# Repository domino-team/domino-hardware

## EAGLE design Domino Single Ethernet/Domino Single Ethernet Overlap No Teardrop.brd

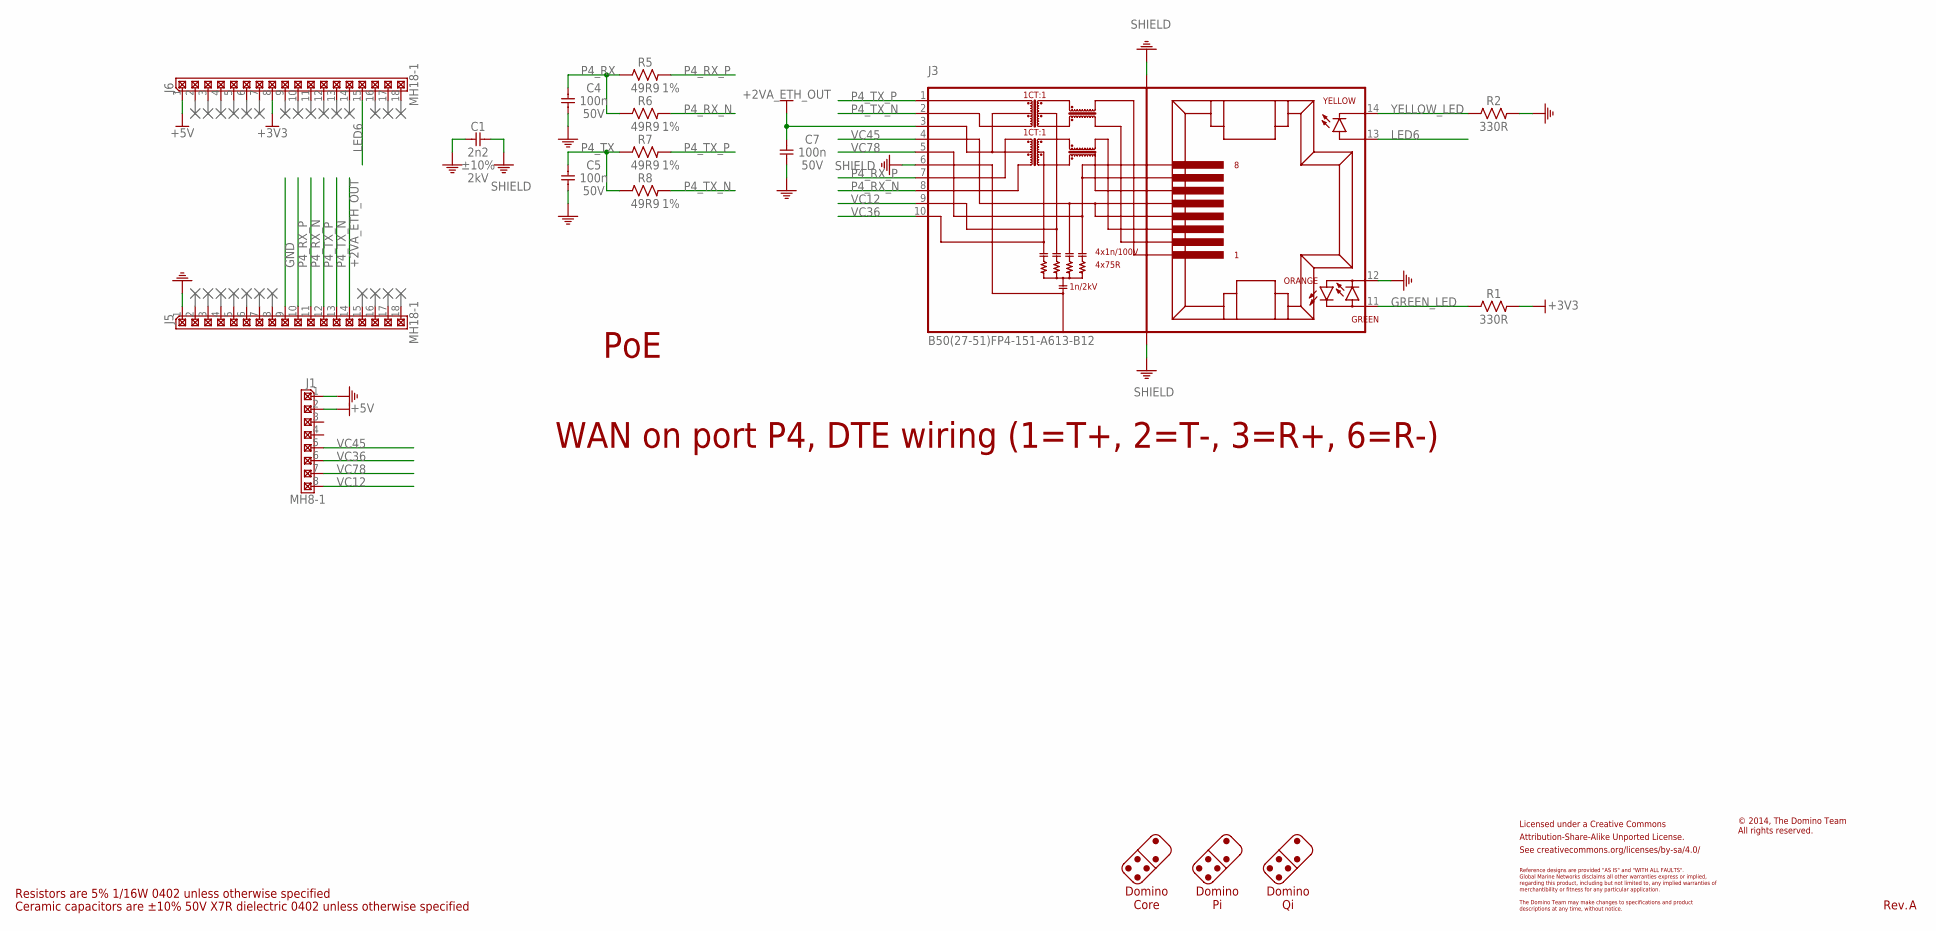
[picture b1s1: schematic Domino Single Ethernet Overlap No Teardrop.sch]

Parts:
C1: 2n2; C1206; PARTNO C1210_2n2_X7R_10%_CER_2kV
C4, C5, C7: 100n; C0402; PARTNO C0402_100n_X7R_10%_CER_50V
CC-BY-SA1: CC-BY-SA_LOGO
J1: MH8-1; MH8-1-0.1
J3: B50(27-51)FP4-151-A613-B12; PARTNO B50(27-51)FP4-151-A613-B12
J5, J6: MH18-1; MH18-1-0.1
R1, R2: 330R; R0402; PARTNO R0402_330R_5%_62.5mW
R5, R6, R7, R8: 49R9; R0402; PARTNO R0402_49R9_1%_62.5mW

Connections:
+2VA_ETH_OUT: C7.2, J3.3, J5.14
+3V3: J6.8, R1.2
+5V: J1.2, J6.1
GND: C1.1, C4.1, C5.1, C7.1, J1.1, J3.12, J5.1, J5.9, R2.2
GREEN_LED: J3.11, R1.1
LED6: J3.13, J6.15
P4_RX: C4.2, R5.1, R6.1
P4_RX_N: J3.8, J5.11, R6.2
P4_RX_P: J3.7, J5.10, R5.2
P4_TX: C5.2, R7.1, R8.1
P4_TX_N: J3.2, J5.13, R8.2
P4_TX_P: J3.1, J5.12, R7.2
SHIELD: C1.2, J3.6, J3.SH$1 (SHIELD), J3.SH$2 (SHIELD)
VC12: J1.8, J3.9
VC36: J1.6, J3.10
VC45: J1.5, J3.4
VC78: J1.7, J3.5
YELLOW_LED: J3.14, R2.1

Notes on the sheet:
Ceramic capacitors are ±10% 50V X7R dielectric 0402 unless otherwise specified
Resistors are 5% 1/16W 0402 unless otherwise specified
Licensed under a Creative Commons
Attribution-Share-Alike Unported License.
See creativecommons.org/licenses/by-sa/4.0/
Reference designs are provided "AS IS" and "WITH ALL FAULTS".
regarding this product, including but not limited to, any implied warranties of
The Domino Team may make changes to specifications and product
Global Marine Networks disclaims all other warranties express or implied,
merchantibility or fitness for any particular application.
descriptions at any time, without notice.
Domino Core
Domino Pi
Domino Qi
© 2014, The Domino Team All rights reserved.
Rev.
WAN on port P4, DTE wiring (1=T+, 2=T-, 3=R+, 6=R-)
PoE

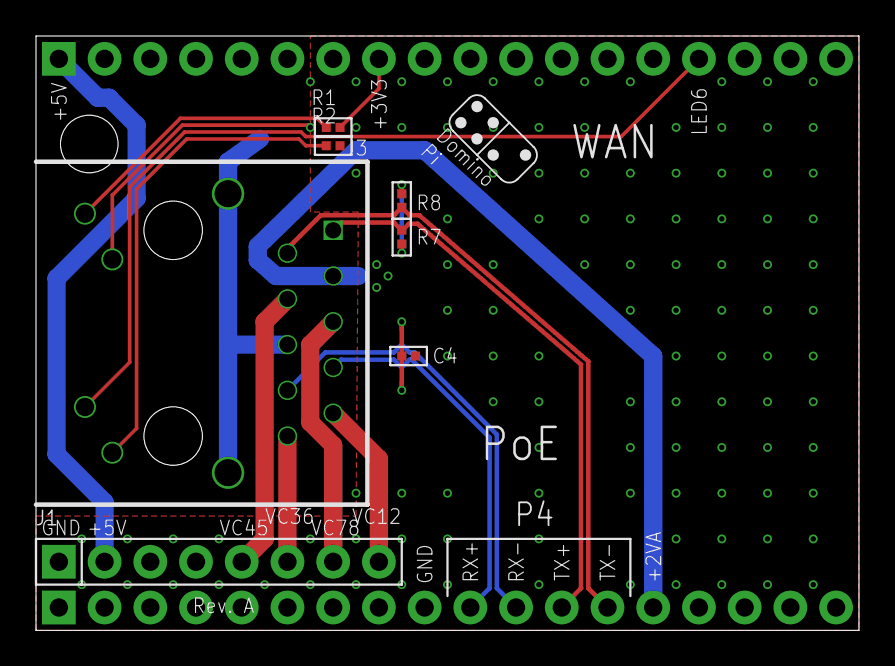
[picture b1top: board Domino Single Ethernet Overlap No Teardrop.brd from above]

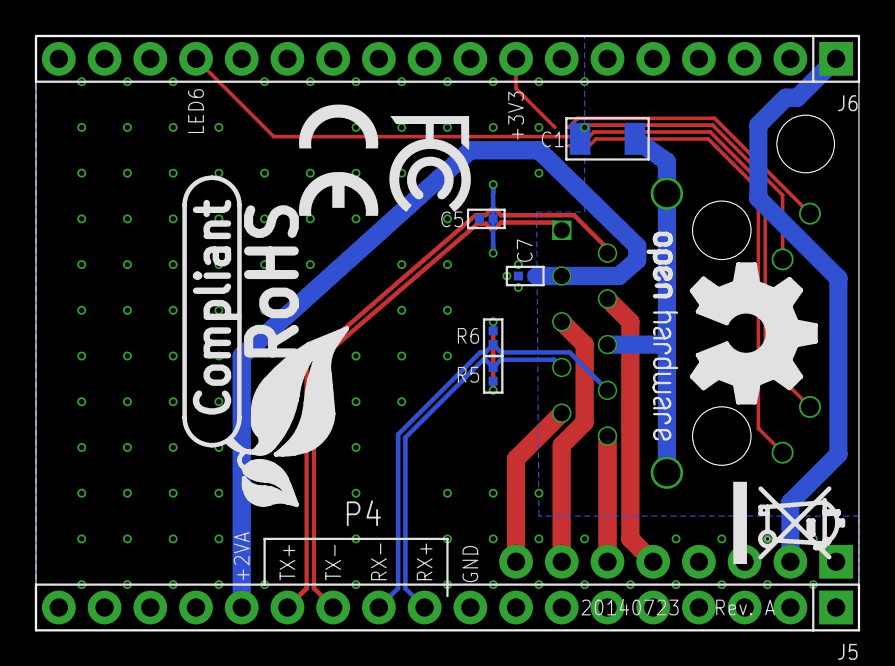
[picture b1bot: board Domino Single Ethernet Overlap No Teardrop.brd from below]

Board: 2 copper layers, 45.7 x 33.0 mm, 23 parts (12 on the bottom side), 18 nets.

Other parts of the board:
DRILEGEND: DRILEGEND
U$3: A5L-LOC
U$4: DOMINO_LOGO_SMALL
U$5: CE_LOGO_SMALL
U$6: FCC_LOGO_SMALL
U$7: OPEN_HARDWARE_LOGO
U$8: RECYCLE_BIN_LOGO
U$9: ROHS_LOGO

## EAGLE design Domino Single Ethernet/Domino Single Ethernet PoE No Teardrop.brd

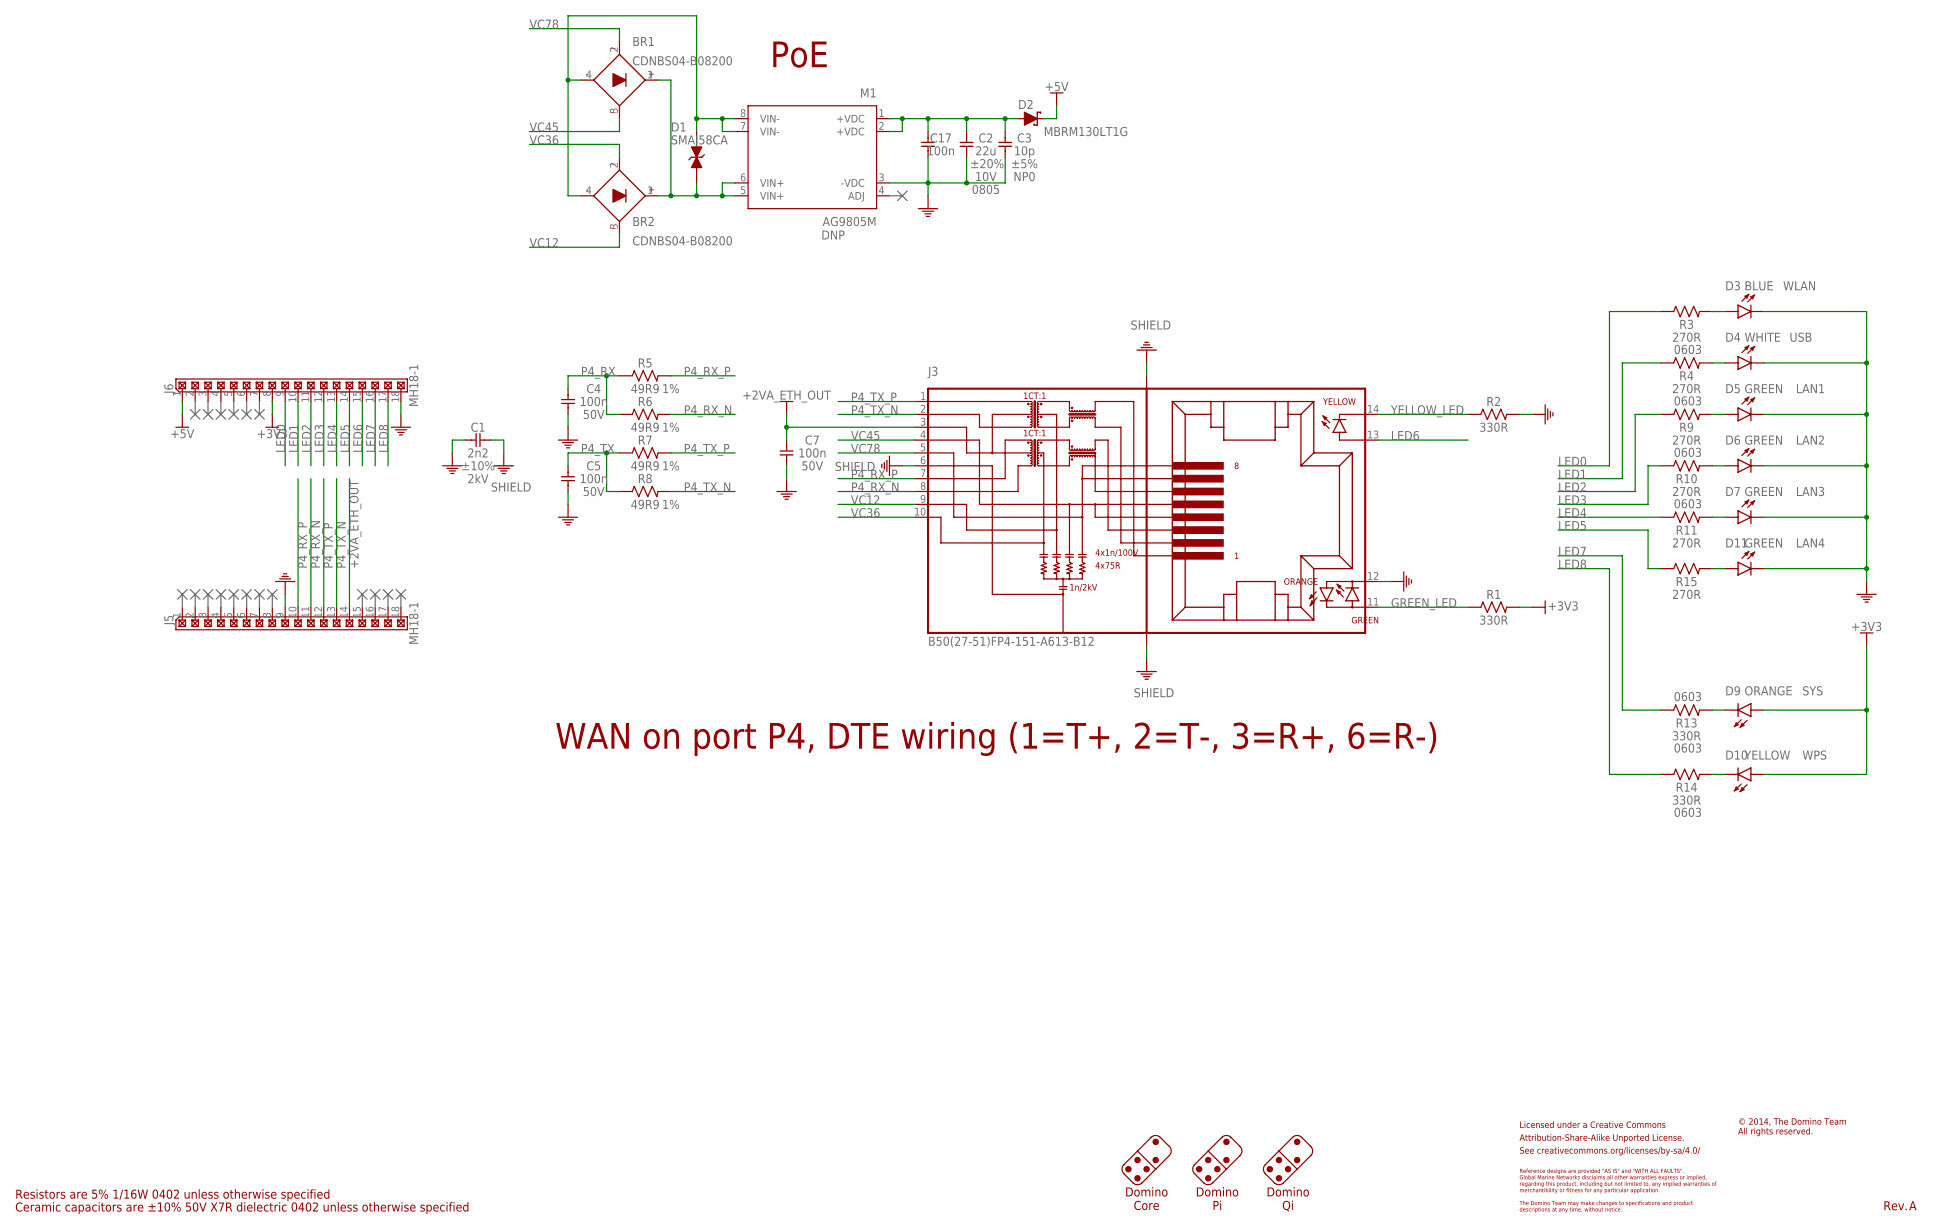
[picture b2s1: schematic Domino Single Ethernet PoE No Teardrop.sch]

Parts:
BR1, BR2: CDNBS04-B08200; NBS04; PARTNO CDNBS04-B08200
C1: 2n2; C1206; PARTNO C1210_2n2_X7R_10%_CER_2kV
C2: 22u; C0805; PARTNO C1206_22u_X7R_20%_CER_10V
C3: 10p; C0402; PARTNO C0402_10p_NP0_5%_CER_50V
C4, C5, C7, C17: 100n; C0402; PARTNO C0402_100n_X7R_10%_CER_50V
CC-BY-SA1: CC-BY-SA_LOGO
D1: SMAJ58CA; SMA
D2: MBRM130LT1G; DO-216AA; PARTNO MBRM130LT1G
D3: BLUE; LED0603; PARTNO LED0603-BLUE
D4: WHITE; LED0603; PARTNO LED0603-WHITE
D5, D6, D7, D11: GREEN; LED0603; PARTNO LED0603-GREEN
D9: ORANGE; LED0603; PARTNO LED0603-ORANGE
D10: YELLOW; LED0603; PARTNO LED0603-YELLOW
J3: B50(27-51)FP4-151-A613-B12; PARTNO B50(27-51)FP4-151-A613-B12
J5, J6: MH18-1; MH18-1-0.1
M1: AG9805M; AG9800M; PARTNO Ag9800M
R1, R2: 330R; R0402; PARTNO R0402_330R_5%_62.5mW
R3, R4, R9, R10, R11, R15: 270R; R0603; PARTNO R0603_270R_5%_125mW
R5, R6, R7, R8: 49R9; R0402; PARTNO R0402_49R9_1%_62.5mW
R13, R14: 330R; R0603; PARTNO R0603_330R_5%_125mW

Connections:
+: BR1.1 (+), BR2.1 (+), D1.C (2), M1.5 (VIN+), M1.6 (VIN+)
+2VA_ETH_OUT: C7.2, J3.3, J5.14
+3V3: D9.2 (A), D10.2 (A), J6.8, R1.2
+5V: D2.1 (C), J6.1
+VDC@1: C2.1, C3.1, C17.1, D2.2 (A), M1.1 (+VDC), M1.2 (+VDC)
-: BR1.4 (-), BR2.4 (-), D1.A (1), M1.7 (VIN-), M1.8 (VIN-)
GND: C1.1, C2.2, C3.2, C4.1, C5.1, C7.1, C17.2, D3.1 (C), D4.1 (C), D5.1 (C), D6.1 (C), D7.1 (C), D11.1 (C), J3.12, J5.9, J6.18, M1.3 (-VDC), R2.2
GREEN_LED: J3.11, R1.1
LED0: J6.9, R3.1
LED1: J6.10, R4.1
LED2: J6.11, R9.1
LED3: J6.12, R10.1
LED4: J6.13, R11.1
LED5: J6.14, R15.1
LED6: J3.13, J6.15
LED7: J6.16, R13.1
LED8: J6.17, R14.1
unnamed: D3.2 (A), R3.2
unnamed: D4.2 (A), R4.2
unnamed: D5.2 (A), R9.2
unnamed: D6.2 (A), R10.2
unnamed: D7.2 (A), R11.2
unnamed: D9.1 (C), R13.2
unnamed: D10.1 (C), R14.2
unnamed: D11.2 (A), R15.2
P4_RX: C4.2, R5.1, R6.1
P4_RX_N: J3.8, J5.11, R6.2
P4_RX_P: J3.7, J5.10, R5.2
P4_TX: C5.2, R7.1, R8.1
P4_TX_N: J3.2, J5.13, R8.2
P4_TX_P: J3.1, J5.12, R7.2
SHIELD: C1.2, J3.6, J3.SH$1 (SHIELD), J3.SH$2 (SHIELD)
VC12: BR2.3 (AC2), J3.9
VC36: BR2.2 (AC1), J3.10
VC45: BR1.3 (AC2), J3.4
VC78: BR1.2 (AC1), J3.5
YELLOW_LED: J3.14, R2.1

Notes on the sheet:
Ceramic capacitors are ±10% 50V X7R dielectric 0402 unless otherwise specified
Resistors are 5% 1/16W 0402 unless otherwise specified
Licensed under a Creative Commons
Attribution-Share-Alike Unported License.
See creativecommons.org/licenses/by-sa/4.0/
Reference designs are provided "AS IS" and "WITH ALL FAULTS".
regarding this product, including but not limited to, any implied warranties of
The Domino Team may make changes to specifications and product
Global Marine Networks disclaims all other warranties express or implied,
merchantibility or fitness for any particular application.
descriptions at any time, without notice.
Domino Core
Domino Pi
Domino Qi
© 2014, The Domino Team All rights reserved.
Rev.
WAN on port P4, DTE wiring (1=T+, 2=T-, 3=R+, 6=R-)
PoE
WLAN
USB
LAN1
LAN2
LAN3
LAN4
SYS
WPS

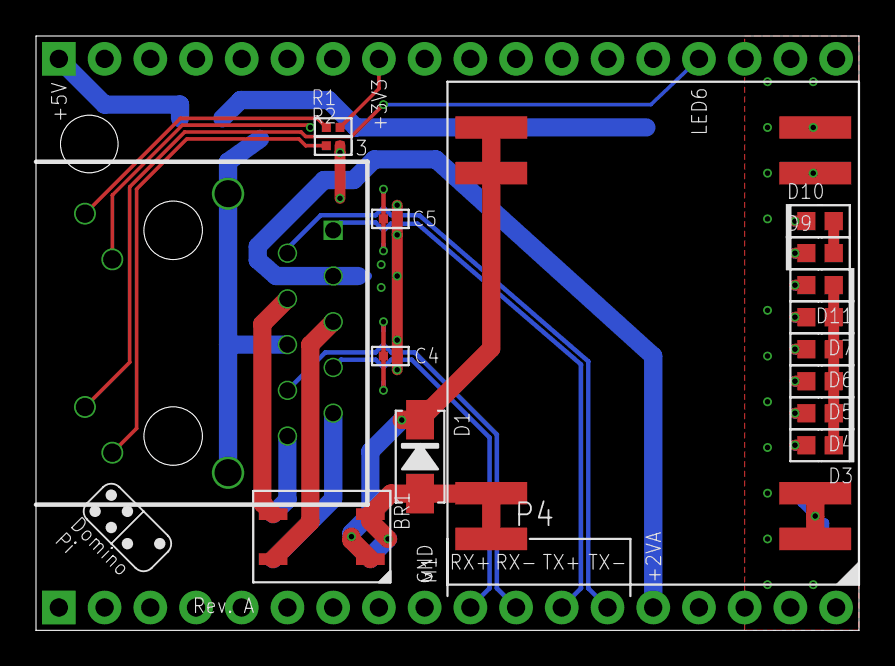
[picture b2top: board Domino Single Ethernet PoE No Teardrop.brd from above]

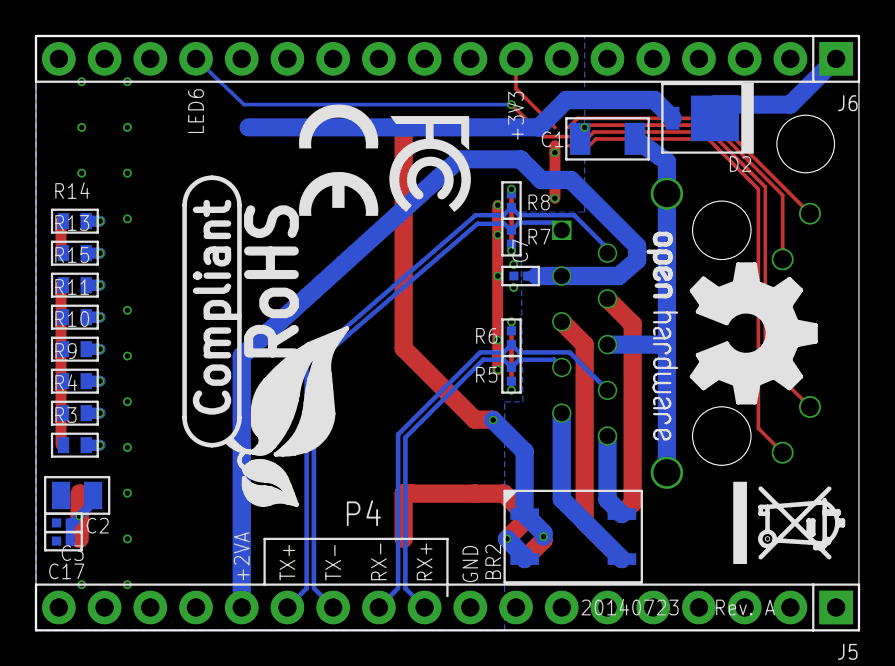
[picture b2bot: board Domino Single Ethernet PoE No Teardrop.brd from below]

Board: 2 copper layers, 45.7 x 33.0 mm, 46 parts (26 on the bottom side), 37 nets.

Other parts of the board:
DRILEGEND: DRILEGEND
U$3: A5L-LOC
U$4: DOMINO_LOGO_SMALL
U$5: CE_LOGO_SMALL
U$6: FCC_LOGO_SMALL
U$7: OPEN_HARDWARE_LOGO
U$8: RECYCLE_BIN_LOGO
U$9: ROHS_LOGO

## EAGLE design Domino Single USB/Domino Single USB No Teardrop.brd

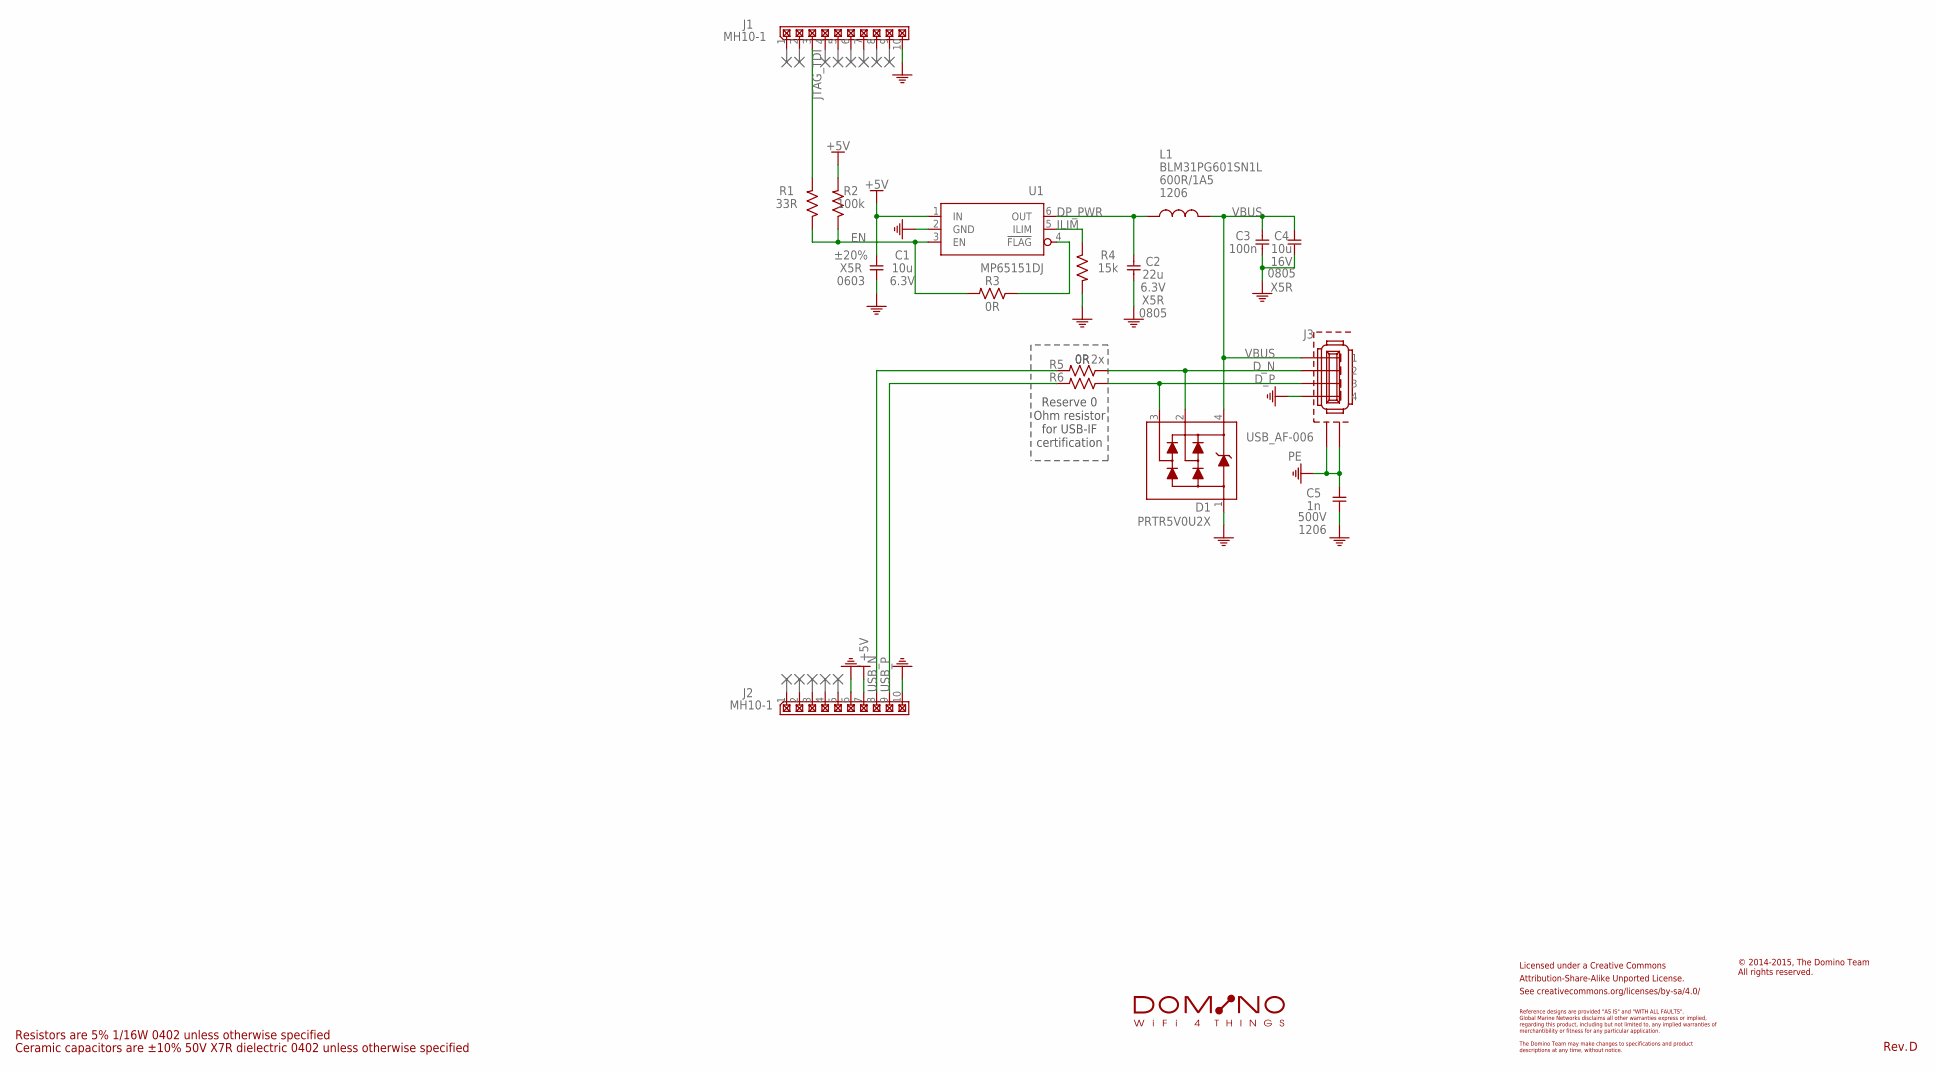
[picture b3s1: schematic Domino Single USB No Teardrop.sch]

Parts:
C1: 10u; C0603; PARTNO C0603_10u_X5R_20%_CER_6V3
C2: 22u; C0805; PARTNO C0805_22u_X5R_20%_CER_6V3
C3: 100n; C0402; PARTNO C0402_100n_X7R_10%_CER_50V
C4: 10u; C0805; PARTNO C0805_10u_X5R_10%_CER_16V
C5: 1n; C1206; PARTNO C1206_1n_X7R_10%_CER_500V
CC-BY-SA1: CC-BY-SA_LOGO
D1: PRTR5V0U2X; SOT143B; PARTNO PRTR5V0U2X
J1, J2: MH10-1; MH10-1-0.1; PARTNO MH10-1-0.1
J3: USB_AF-006; PARTNO USB_AF-006
L1: BLM31PG601SN1L; FB1206; PARTNO BLM31PG601SN1L
R1: 33R; R0402; PARTNO R0402_33R_5%_62.5mW
R2: 100k; R0402; PARTNO R0402_100k_5%_62.5mW
R3, R5, R6: 0R; R0402; PARTNO R0402_0R_5%_62.5mW
R4: 15k; R0402; PARTNO R0402_15k_5%_62.5mW
S1: DOMINO_LOGO
U1: MP65151DJ; SOT23-6; PARTNO MP65151DJ

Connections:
+5V: C1.1, J2.7, R2.2, U1.1 (IN)
DP_PWR: C2.1, L1.1, U1.6 (OUT)
D_N: D1.2, J3.2, R5.1
D_P: D1.3, J3.3, R6.1
EN: R1.1, R2.1, R3.2, U1.3 (EN)
GND: C1.2, C2.2, C3.2, C4.2, C5.2, D1.1, J1.10, J2.6, J2.10, J3.4, R4.2, U1.2 (GND)
ILIM: R4.1, U1.5 (ILIM)
JTAG_TDI: J1.3, R1.2
unnamed: R3.1, U1.4 (!FLAG)
PE: C5.1, J3.S$1 (G), J3.S$2 (G)
USB_N: J2.8, R5.2
USB_P: J2.9, R6.2
VBUS: C3.1, C4.1, D1.4, J3.1, L1.2

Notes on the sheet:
Ceramic capacitors are ±10% 50V X7R dielectric 0402 unless otherwise specified
Resistors are 5% 1/16W 0402 unless otherwise specified
Licensed under a Creative Commons
Attribution-Share-Alike Unported License.
See creativecommons.org/licenses/by-sa/4.0/
Reference designs are provided "AS IS" and "WITH ALL FAULTS".
regarding this product, including but not limited to, any implied warranties of
The Domino Team may make changes to specifications and product
Global Marine Networks disclaims all other warranties express or implied,
merchantibility or fitness for any particular application.
descriptions at any time, without notice.
© 2014-2015, The Domino Team All rights reserved.
Rev.
Reserve 0 Ohm resistor for USB-IF certification

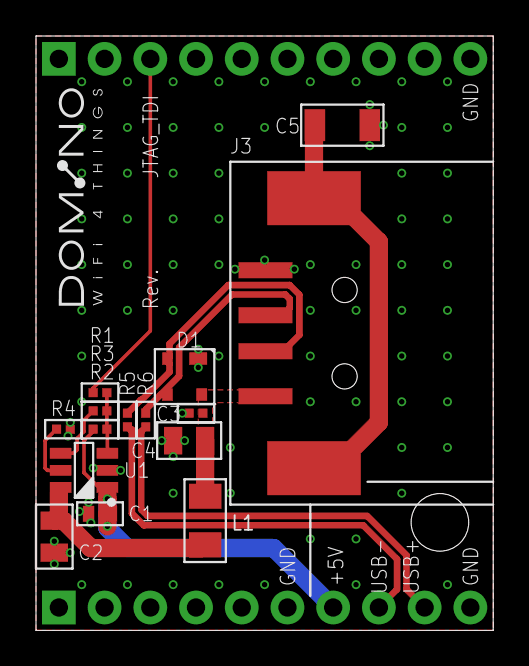
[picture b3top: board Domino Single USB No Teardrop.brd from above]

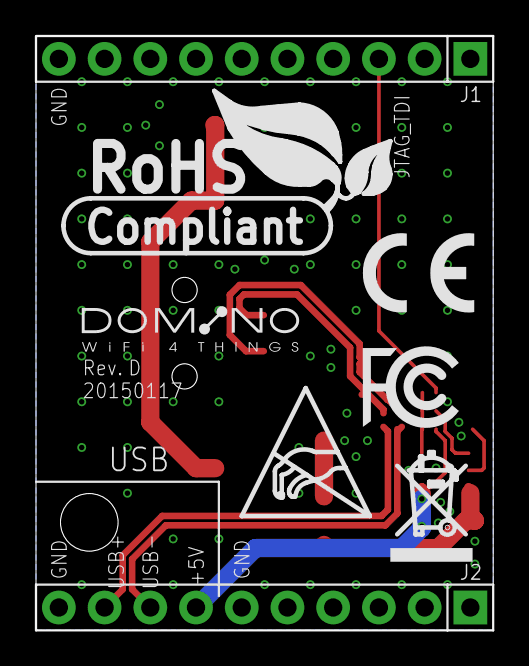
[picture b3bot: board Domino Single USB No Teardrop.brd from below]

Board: 2 copper layers, 25.4 x 33.0 mm, 28 parts (8 on the bottom side), 13 nets.

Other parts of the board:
DRILEGEND: DRILEGEND
U$1: ROHS_LOGO
U$3: A5L-LOC
U$4, U$10: DOMINO_LOGO_SMALL
U$5: CE_LOGO_SMALL
U$6: FCC_LOGO_SMALL
U$8: RECYCLE_BIN_LOGO
U$11: ESD_LOGO

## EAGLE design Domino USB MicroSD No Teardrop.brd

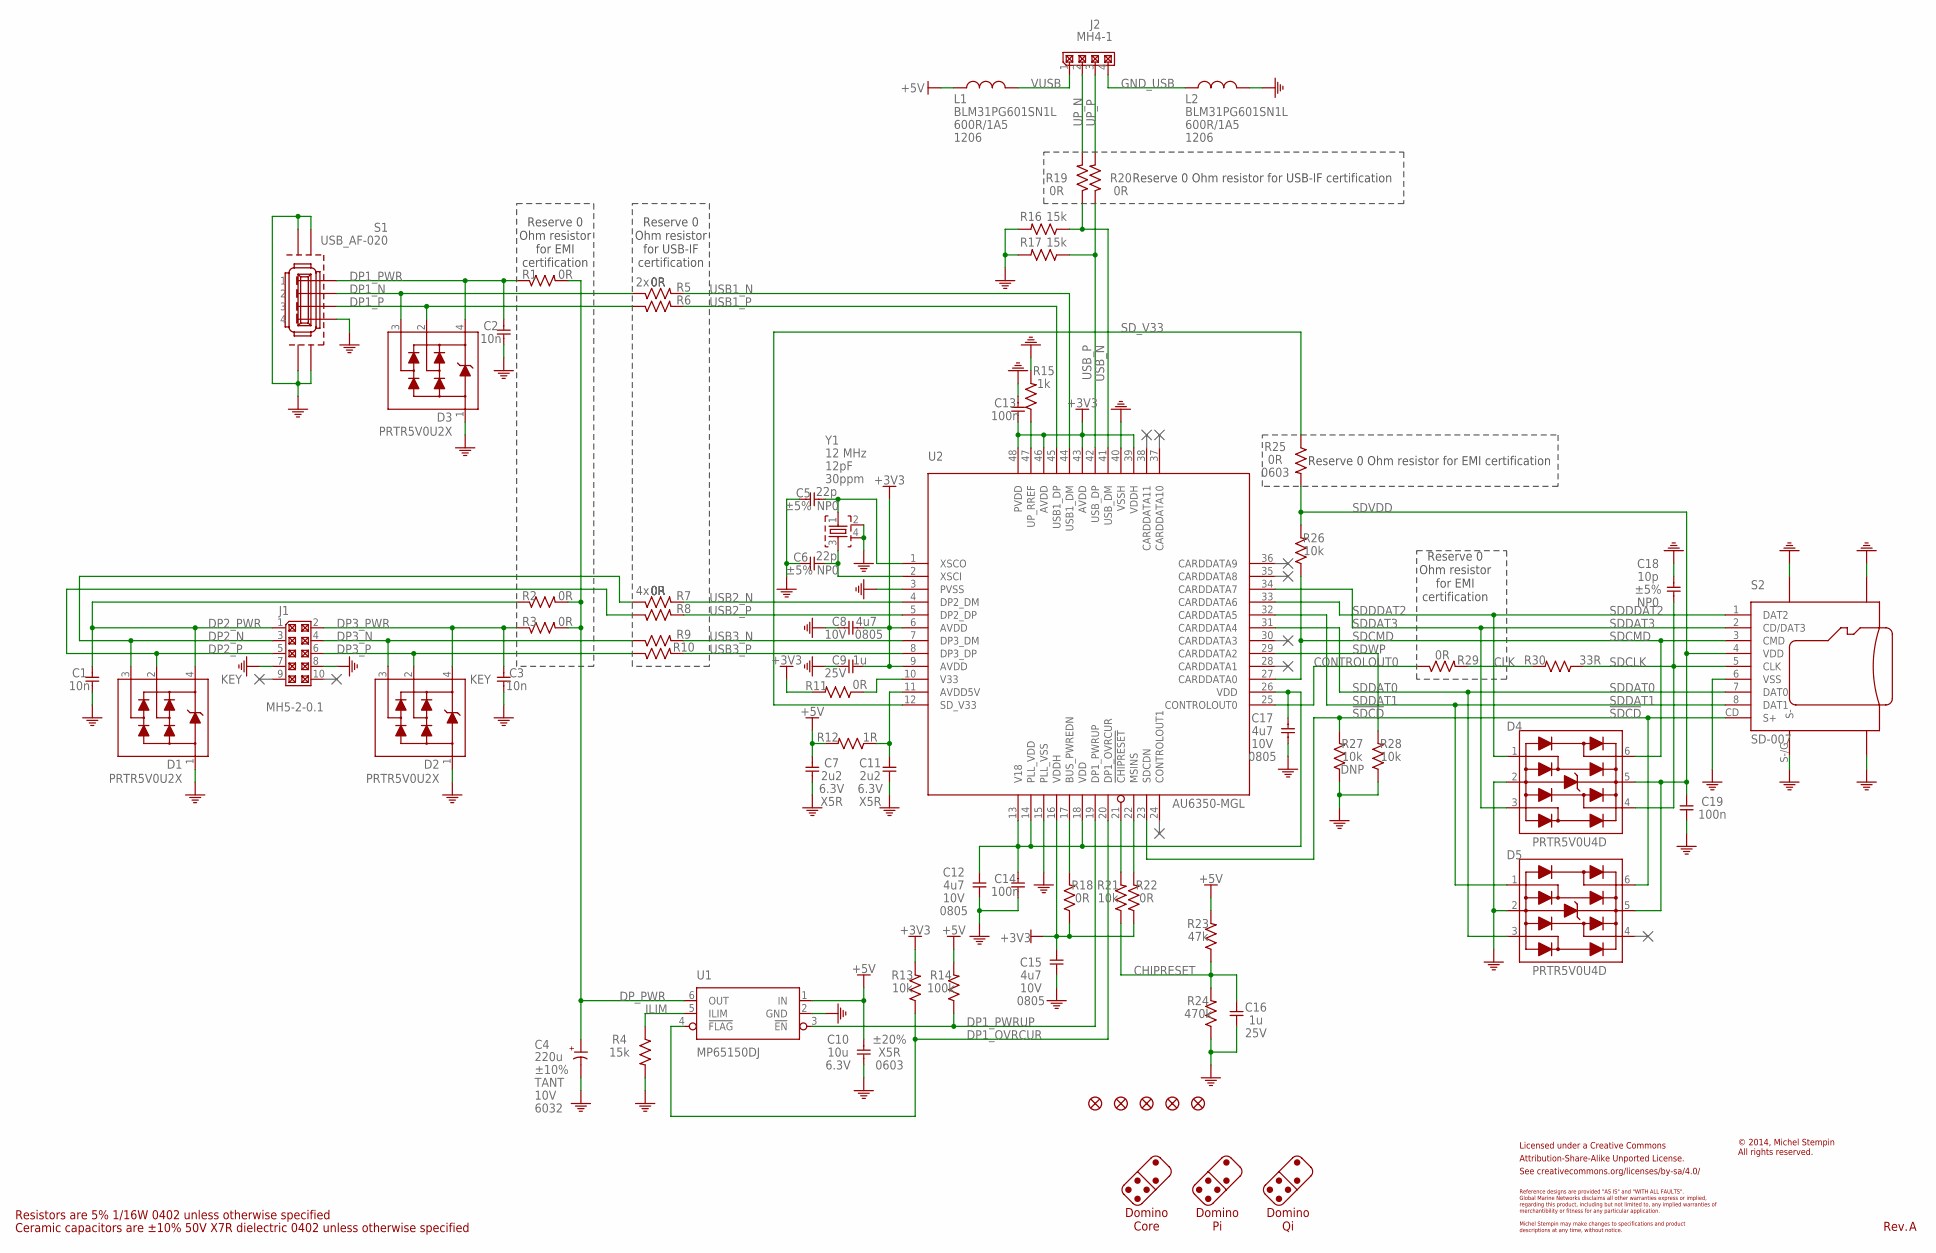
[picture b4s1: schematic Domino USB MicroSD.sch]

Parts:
C1, C2, C3: 10n; C0402; PARTNO C0402_10n_X7R_10%_CER_50V
C4: 220u; C/6032-25; PARTNO CPOLC-6032_220u_20%_TANT_10V
C5, C6: 22p; C0402; PARTNO C0402_22p_NP0_5%_CER_50V
C7, C11: 2u2; C0402; PARTNO C0402_2u2_X5R_10%_CER_6V3
C8, C12, C15, C17: 4u7; C0805; PARTNO C0805_4u7_X7R_10%_CER_6V3
C9, C16: 1u; C0402; PARTNO C0402_1u_X7R_10%_CER_25V
C10: 10u; C0603; PARTNO C0603_10u_X5R_20%_CER_6V3
C13, C14, C19: 100n; C0402; PARTNO C0402_100n_X7R_10%_CER_50V
C18: 10p; C0402; PARTNO C0402_10p_NP0_5%_CER_50V
CC-BY-SA1: CC-BY-SA_LOGO
D1, D2, D3: PRTR5V0U2X; SOT143B; PARTNO PRTR5V0U2X
D4, D5: PRTR5V0U4D; SOT23-6; PARTNO PRTR5V0U4D
F1, F2, F4, F5, F6: FIDUCIAL
J1: MH5-2-0.1; MH05-2-0.1; PARTNO MH5-2-0.1
J2: MH4-1; MH4-1-0.1; PARTNO MH4-1-0.1
L1, L2: BLM31PG601SN1L; FB1206; PARTNO BLM31PG601SN1L
R1, R2, R3, R5, R6, R7, R8, R9, R10, R11, R18, R19, R20, R22, R29: 0R; R0402; PARTNO R0402_0R_5%_62.5mW
R4, R16, R17: 15k; R0402; PARTNO R0402_15k_5%_62.5mW
R12: 1R; R0402; PARTNO R0402_1R_5%_62.5mW
R13, R21, R26, R27, R28: 10k; R0402; PARTNO R0402_10k_5%_62.5mW
R14: 100k; R0402; PARTNO R0402_100k_5%_62.5mW
R15: 1k; R0402; PARTNO R0402_1k_5%_62.5mW
R23: 47k; R0402; PARTNO R0402_47k_5%_62.5mW
R24: 470k; R0402; PARTNO R0402_470k_5%_62.5mW
R25: 0R; R0603; PARTNO R0603_0R_5%_125mW
R30: 33R; R0402; PARTNO R0402_33R_5%_62.5mW
S1: USB_AF-020; PARTNO USB_AF-020
S2: SD-007; PARTNO SD-007
U1: MP65150DJ; SOT23-6; PARTNO MP65150DJ
U2: AU6350-MGL; LQFP-48_7X7; PARTNO AU6350-MGL
Y1: 12 MHz; CRYSTAL_32X25; PARTNO CRYSTAL_32X25_2SH_12PF_30PPM

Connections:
!CHIPRESET: R21.2, U2.21 (!CHIPRESET)
!SDCD: D5.6 (I/O4), R27.2, S2.CD (S+), U2.23 (SDCDN)
+3V3: C8.2, C9.2, C13.2, C15.2, R11.2, R13.2, R18.1, R22.1, U2.6 (AVDD), U2.9 (AVDD), U2.16 (VDDH), U2.39 (VDDH), U2.43 (AVDD), U2.46 (AVDD), U2.48 (PVDD)
+5V: C7.1, C10.1, L1.2, R12.2, R14.2, R23.2, U1.1 (IN)
AVDD5V: C11.1, R12.1, U2.11 (AVDD5V)
BUS_PWREDN: R18.2, U2.17 (BUS_PWREDN)
CHIPRESET: C16.1, R21.1, R23.1, R24.2
CLK: R29.2, R30.2
CONTROLOUT0: R29.1, U2.25 (CONTROLOUT0)
DP1_N: D3.3, R5.1, S1.2
DP1_OVRCUR: R13.1, U1.4 (!FLAG), U2.20 (DP1_OVRCUR)
DP1_P: D3.2, R6.1, S1.3
DP1_PWR: C2.1, D3.4, R1.1, S1.1
DP1_PWRUP: R14.1, U1.3 (!EN), U2.19 (DP1_PWRUP)
DP2_N: D1.3, J1.3, R7.1
DP2_P: D1.2, J1.5, R8.1
DP2_PWR: C1.1, D1.4, J1.1, R2.1
DP3_N: D2.3, J1.4, R9.1
DP3_P: D2.2, J1.6, R10.1
DP3_PWR: C3.1, D2.4, J1.2, R3.1
DP_PWR: C4.1 (+), R1.2, R2.2, R3.2, U1.6 (OUT)
GND: C1.2, C2.2, C3.2, C4.2 (-), C5.1, C6.1, C7.2, C8.1, C9.1, C10.2, C11.2, C12.1, C13.1, C14.2, C15.1, C16.2, C17.1, C18.2, C19.2, D1.1, D2.1, D3.1, D4.2 (GND), D5.2 (GND), J1.7, J1.8, L2.1, R4.2, R15.2, R16.2, R17.2, R24.1, R27.1, R28.1, S1.4, S1.G$1 (G), S1.G$2 (G), S1.G$3 (G), S1.G$4 (G), S2.6 (VSS), S2.G$1 (G), S2.G$2 (G), S2.G$3 (G), S2.S-/G (S-), U1.2 (GND), U2.3 (PVSS), U2.15 (PLL_VSS), U2.40 (VSSH), Y1.2, Y1.4
GND_USB: J2.4, L2.2
ILIM: R4.1, U1.5 (ILIM)
MSINS: R22.2, U2.22 (MSINS)
SDCLK: C18.1, D4.4 (I/O3), R30.1, S2.5 (CLK)
SDCMD: D4.6 (I/O4), R26.1, S2.3 (CMD), U2.27 (CARDDATA0)
SDDAT0: D5.3 (I/O2), S2.7 (DAT0), U2.31 (CARDDATA4)
SDDAT1: D5.1 (I/O1), S2.8 (DAT1), U2.32 (CARDDATA5)
SDDAT3: D4.3 (I/O2), S2.2 (CD/DAT3), U2.34 (CARDDATA7)
SDDDAT2: D4.1 (I/O1), S2.1 (DAT2), U2.33 (CARDDATA6)
SDVDD: C19.1, D4.5 (VCC), D5.5 (VCC), R25.2, R26.2, S2.4 (VDD)
SDWP: R28.2, U2.29 (CARDDATA2)
SD_V33: R25.1, U2.12 (SD_V33)
UP_N: J2.2, R19.2
UP_P: J2.3, R20.2
UP_PREF: R15.1, U2.47 (UP_RREF)
USB1_N: R5.2, U2.44 (USB1_DM)
USB1_P: R6.2, U2.45 (USB1_DP)
USB2_N: R7.2, U2.4 (DP2_DM)
USB2_P: R8.2, U2.5 (DP2_DP)
USB3_N: R9.2, U2.7 (DP3_DM)
USB3_P: R10.2, U2.8 (DP3_DP)
USB_N: R16.1, R19.1, U2.41 (USB_DM)
USB_P: R17.1, R20.1, U2.42 (USB_DP)
V18: C12.2, C14.1, C17.2, U2.13 (V18), U2.14 (PLL_VDD), U2.18 (VDD), U2.26 (VDD)
V33: R11.1, U2.10 (V33)
VUSB: J2.1, L1.1
XSCI: C6.2, U2.2 (XSCI), Y1.3
XSCO: C5.2, U2.1 (XSCO), Y1.1

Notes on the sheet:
Ceramic capacitors are ±10% 50V X7R dielectric 0402 unless otherwise specified
Resistors are 5% 1/16W 0402 unless otherwise specified
Licensed under a Creative Commons
Attribution-Share-Alike Unported License.
See creativecommons.org/licenses/by-sa/4.0/
Reference designs are provided "AS IS" and "WITH ALL FAULTS".
regarding this product, including but not limited to, any implied warranties of
Michel Stempin may make changes to specifications and product
Global Marine Networks disclaims all other warranties express or implied,
merchantibility or fitness for any particular application.
descriptions at any time, without notice.
Domino Core
Domino Pi
Domino Qi
© 2014, Michel Stempin All rights reserved.
Rev.
KEY
Reserve 0 Ohm resistor for EMI certification
Reserve 0 Ohm resistor for EMI certification
Reserve 0 Ohm resistor for USB-IF certification
Reserve 0 Ohm resistor for USB-IF certification

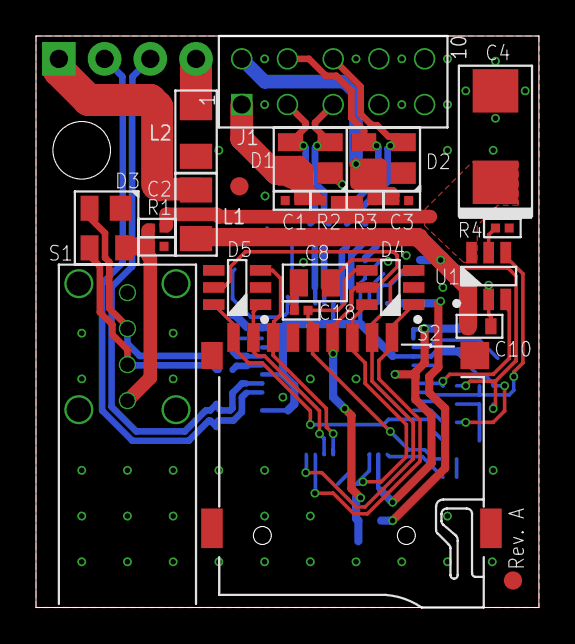
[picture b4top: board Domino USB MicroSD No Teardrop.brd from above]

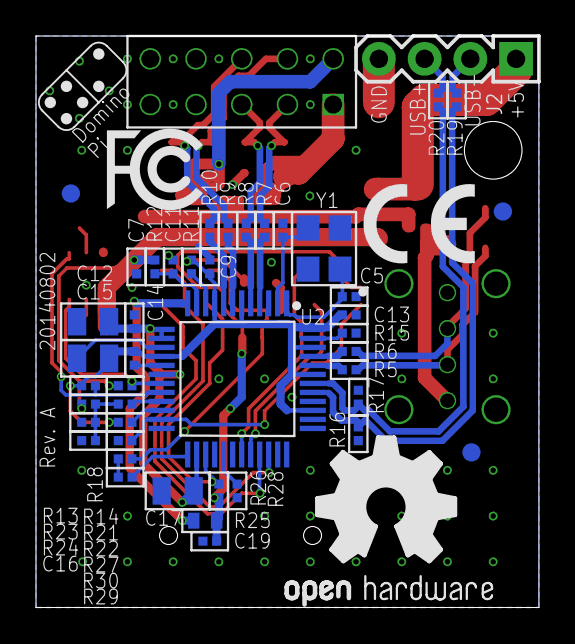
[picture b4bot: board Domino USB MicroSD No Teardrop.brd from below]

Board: 2 copper layers, 27.9 x 31.8 mm, 75 parts (48 on the bottom side), 50 nets.

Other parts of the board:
DRILEGEND: DRILEGEND
U$3: A5L-LOC
U$4: DOMINO_LOGO_SMALL
U$13: CE_LOGO_SMALL
U$15: FCC_LOGO_SMALL
U$16: OPEN_HARDWARE_LOGO

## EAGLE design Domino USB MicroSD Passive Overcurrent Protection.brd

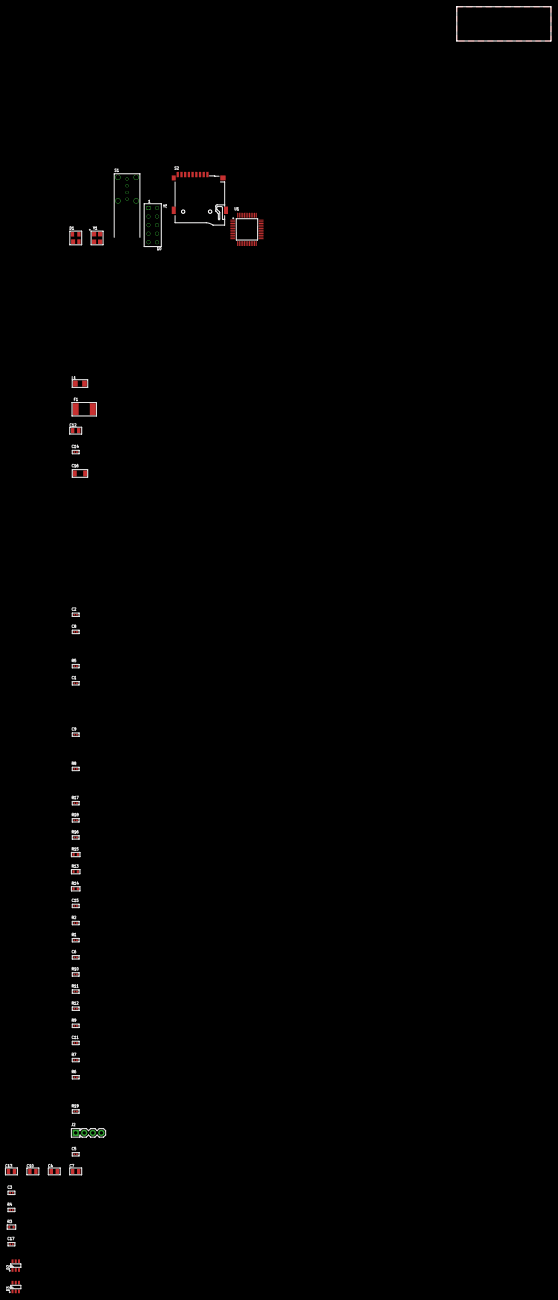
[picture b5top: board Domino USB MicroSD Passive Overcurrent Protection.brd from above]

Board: 2 copper layers, 27.9 x 10.2 mm, 51 parts (1 on the bottom side), 38 nets, no tracks yet.

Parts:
C1, C2: 22p; C0402
C3, C6: 2u2; C0402
C4, C7, C10, C13: 4u7; C0805
C5, C11: 1u; C0402
C8, C9, C14, C15: 100n; C0402
C12: 10u; C0805
C16: 1n; C1206
C17: 10p; C0402
CC-BY-SA1: CC-BY-SA_LOGO
D1: YSSR05; SOT143B
D2, D3: PJSDA05C-4; SOT23-6
DRILEGEND: DRILEGEND
F1: 0ZCG0110FF2C; PTC1812
J1: MH5-2-0.1; MH05-2-0.1
J2: MH4-1; MH4-1-0.1
L1: BLM31PG601SN1L; FB1206
R1, R2, R9, R16, R17, R18: 10k; R0402
R3, R13, R14, R15: 0R; R0603
R4: 1R; R0402
R5: 1k; R0402
R6, R7: 15k; R0402
R8, R10: 0R; R0402
R11: 47k; R0402
R12: 470k; R0402
R19: 33R; R0402
S1: USB_AF-020
S2: SD-007
U1: AU6350-MGL; LQFP-48_7X7
U$3: A5L-LOC
U$4: DOMINO_LOGO_SMALL
Y1: 12 MHz; CRYSTAL_32X25

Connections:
!CHIPRESET: R9.2, U1.21
!SDCD: D3.3, R17.2, S2.CD, U1.23
+3V3: C4.2, C5.2, C8.2, C10.2, R3.2, R8.1, R10.1, U1.6, U1.9, U1.16, U1.39, U1.43, U1.46, U1.48
+5V: C3.1, J2.1, L1.2, R4.2, R11.2
BUS_PWREDN: R8.2, U1.17
CHIPRESET: C11.1, R9.1, R11.1, R12.2
CONTROLOUT0: R19.2, U1.25
DP1_DM: D1.3, R13.1, S1.2
DP1_DP: D1.2, R14.1, S1.3
DP1_OVRCUR: R1.1, R2.2, U1.20
DP2_DM: J1.3, U1.4
DP2_DP: J1.5, U1.5
DP3_DM: J1.4, U1.7
DP3_DP: J1.6, U1.8
GND: C1.1, C2.1, C3.2, C4.1, C5.1, C6.2, C7.1, C8.1, C9.2, C10.1, C11.2, C12.2, C13.1, C14.2, C15.2, C16.2, C17.2, D1.1, D2.2, D2.5, D3.2, D3.5, J1.7, J1.8, J2.4, R2.1, R5.2, R6.2, R7.2, R12.1, R17.1, R18.1, S1.4, S2.6, S2.G$1, S2.G$2, S2.G$3, S2.S-/G, U1.3, U1.15, U1.40, Y1.2, Y1.4
MSINS: R10.2, U1.22
unnamed: F1.1, L1.1
unnamed: C6.1, R4.1, U1.11
unnamed: R3.1, U1.10
SDCLK: C17.1, D2.4, R19.1, S2.5
SDCMD: D2.3, R16.1, S2.3, U1.27
SDDAT0: D3.1, S2.7, U1.31
SDDAT1: D3.6, S2.8, U1.32
SDDAT3: D2.6, S2.2, U1.34
SDDDAT2: D2.1, S2.1, U1.33
SDVDD: C15.1, R15.2, R16.2, S2.4
SDWP: R18.2, U1.29
SD_V33: R15.1, U1.12
SHIELD: C16.1, J1.10, S1.G$1, S1.G$2, S1.G$3, S1.G$4
UP_PREF: R5.1, U1.47
USB1_DM: R13.2, U1.44
USB1_DP: R14.2, U1.45
USB_DM: J2.2, R6.1, U1.41
USB_DP: J2.3, R7.1, U1.42
V18: C7.2, C9.1, C13.2, U1.13, U1.14, U1.18, U1.26
VBUS: C12.1, C14.1, D1.4, F1.2, J1.1, J1.2, R1.2, S1.1
XSCI: C2.2, U1.2, Y1.3
XSCO: C1.2, U1.1, Y1.1

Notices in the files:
parts and their libraries:
Domino: See creativecommons.org/licenses/by-sa/4.0/ for details.
Domino: See creativecommons.org/licenses/by-sa/3.0/ for details.
Domino: Copyright © 2012, Michel Stempin, All rights reserved
Licenced under Creative Commons CC BY-SA 3.0 license.
